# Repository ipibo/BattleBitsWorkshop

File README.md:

# BattleBitsWorkshop
Repo with info about the Battle Bits Workshop

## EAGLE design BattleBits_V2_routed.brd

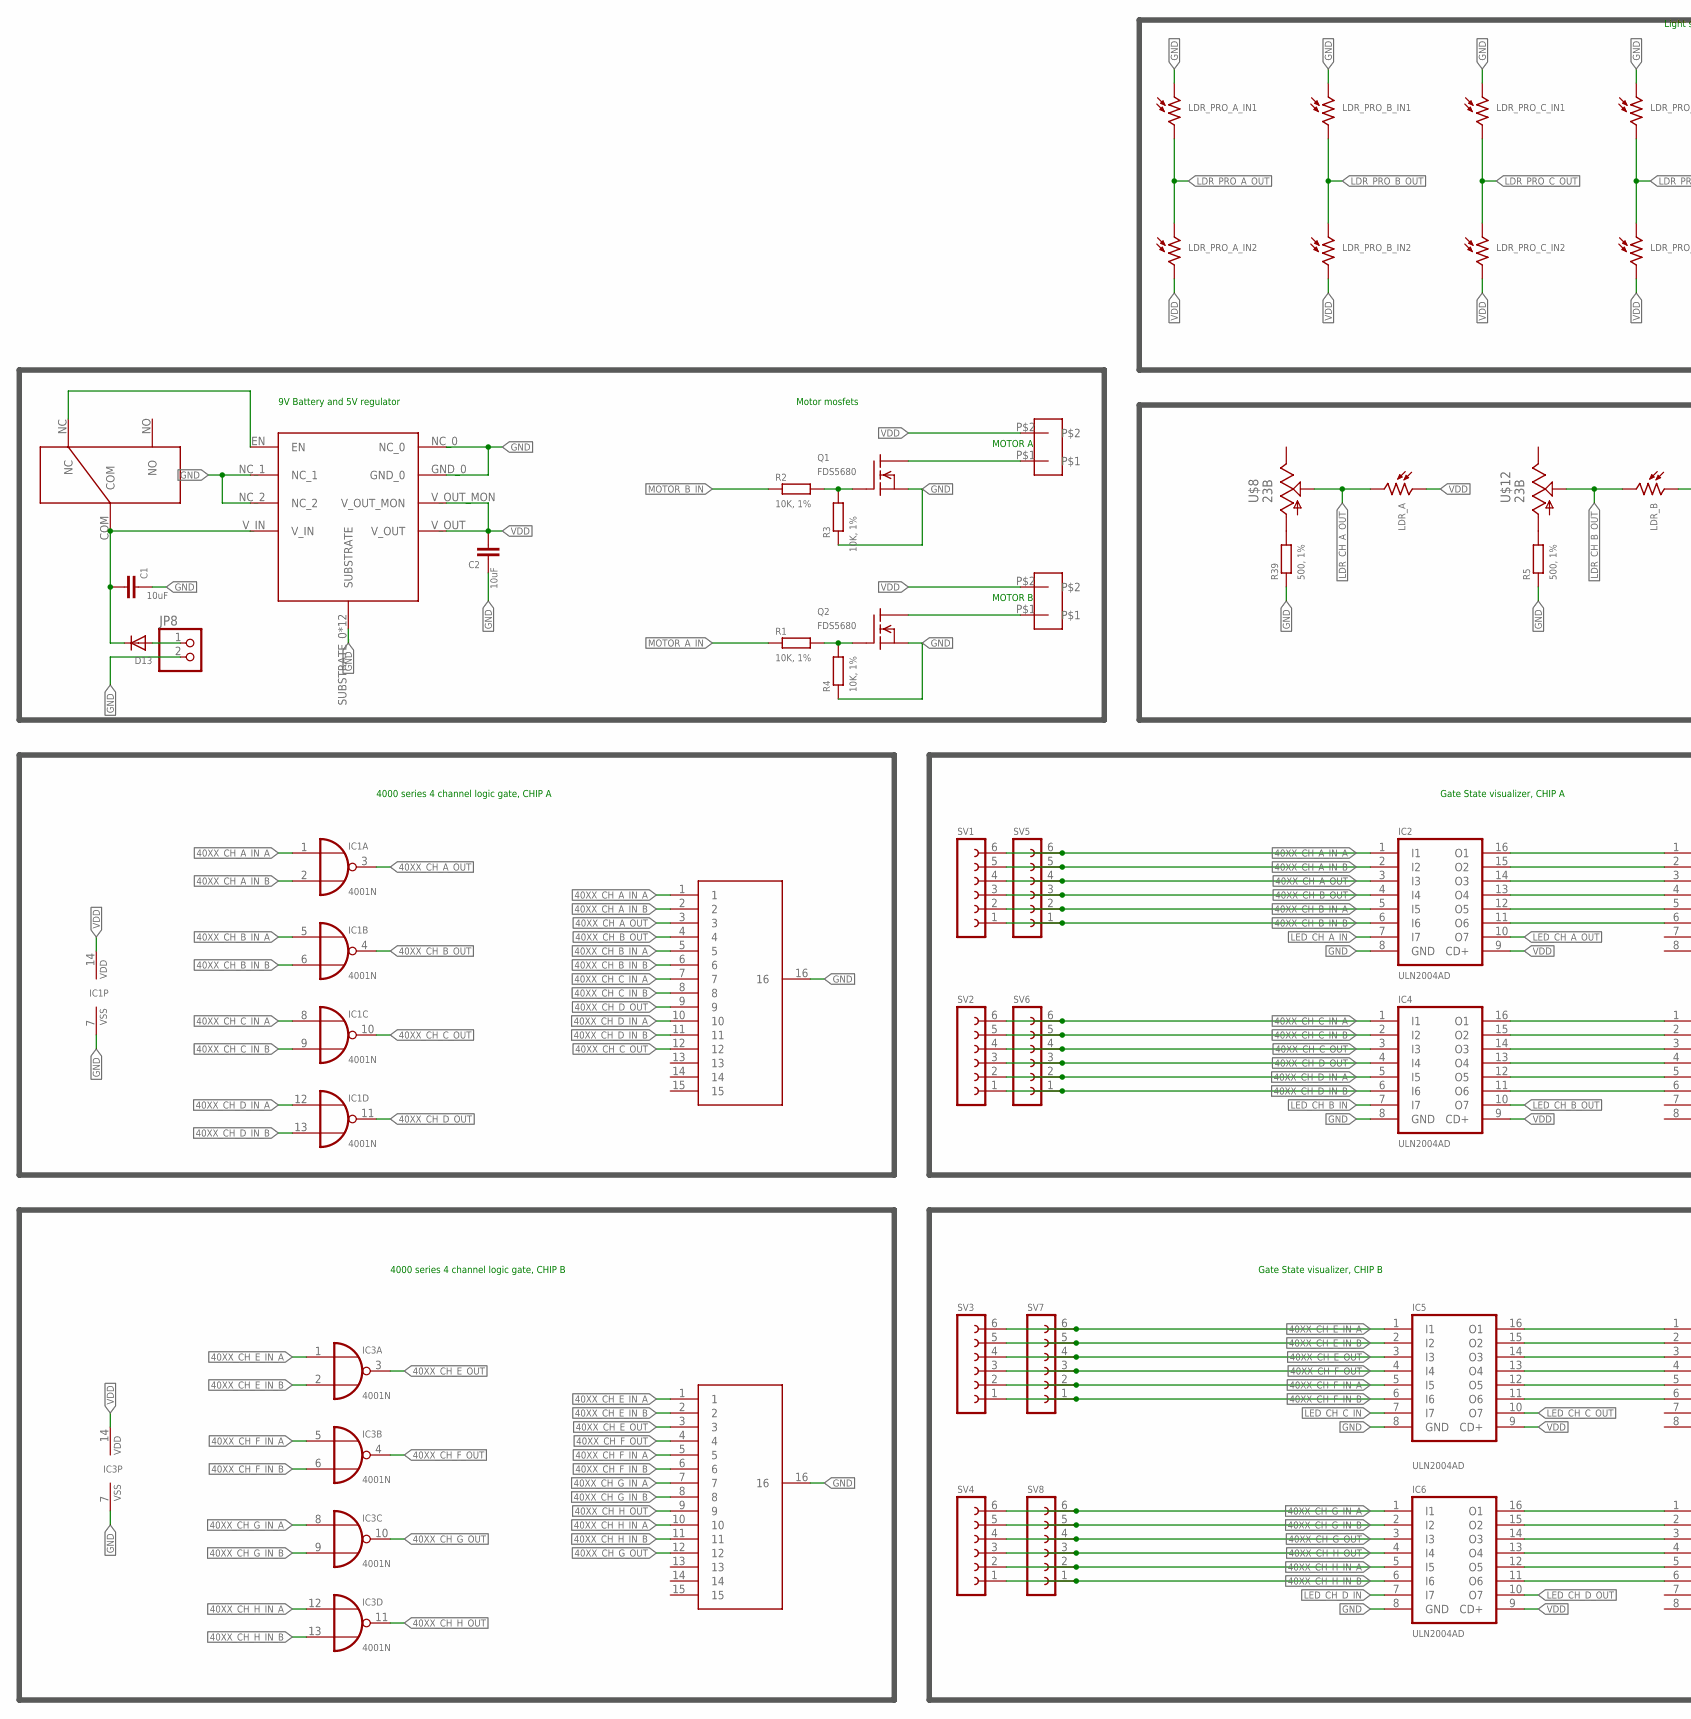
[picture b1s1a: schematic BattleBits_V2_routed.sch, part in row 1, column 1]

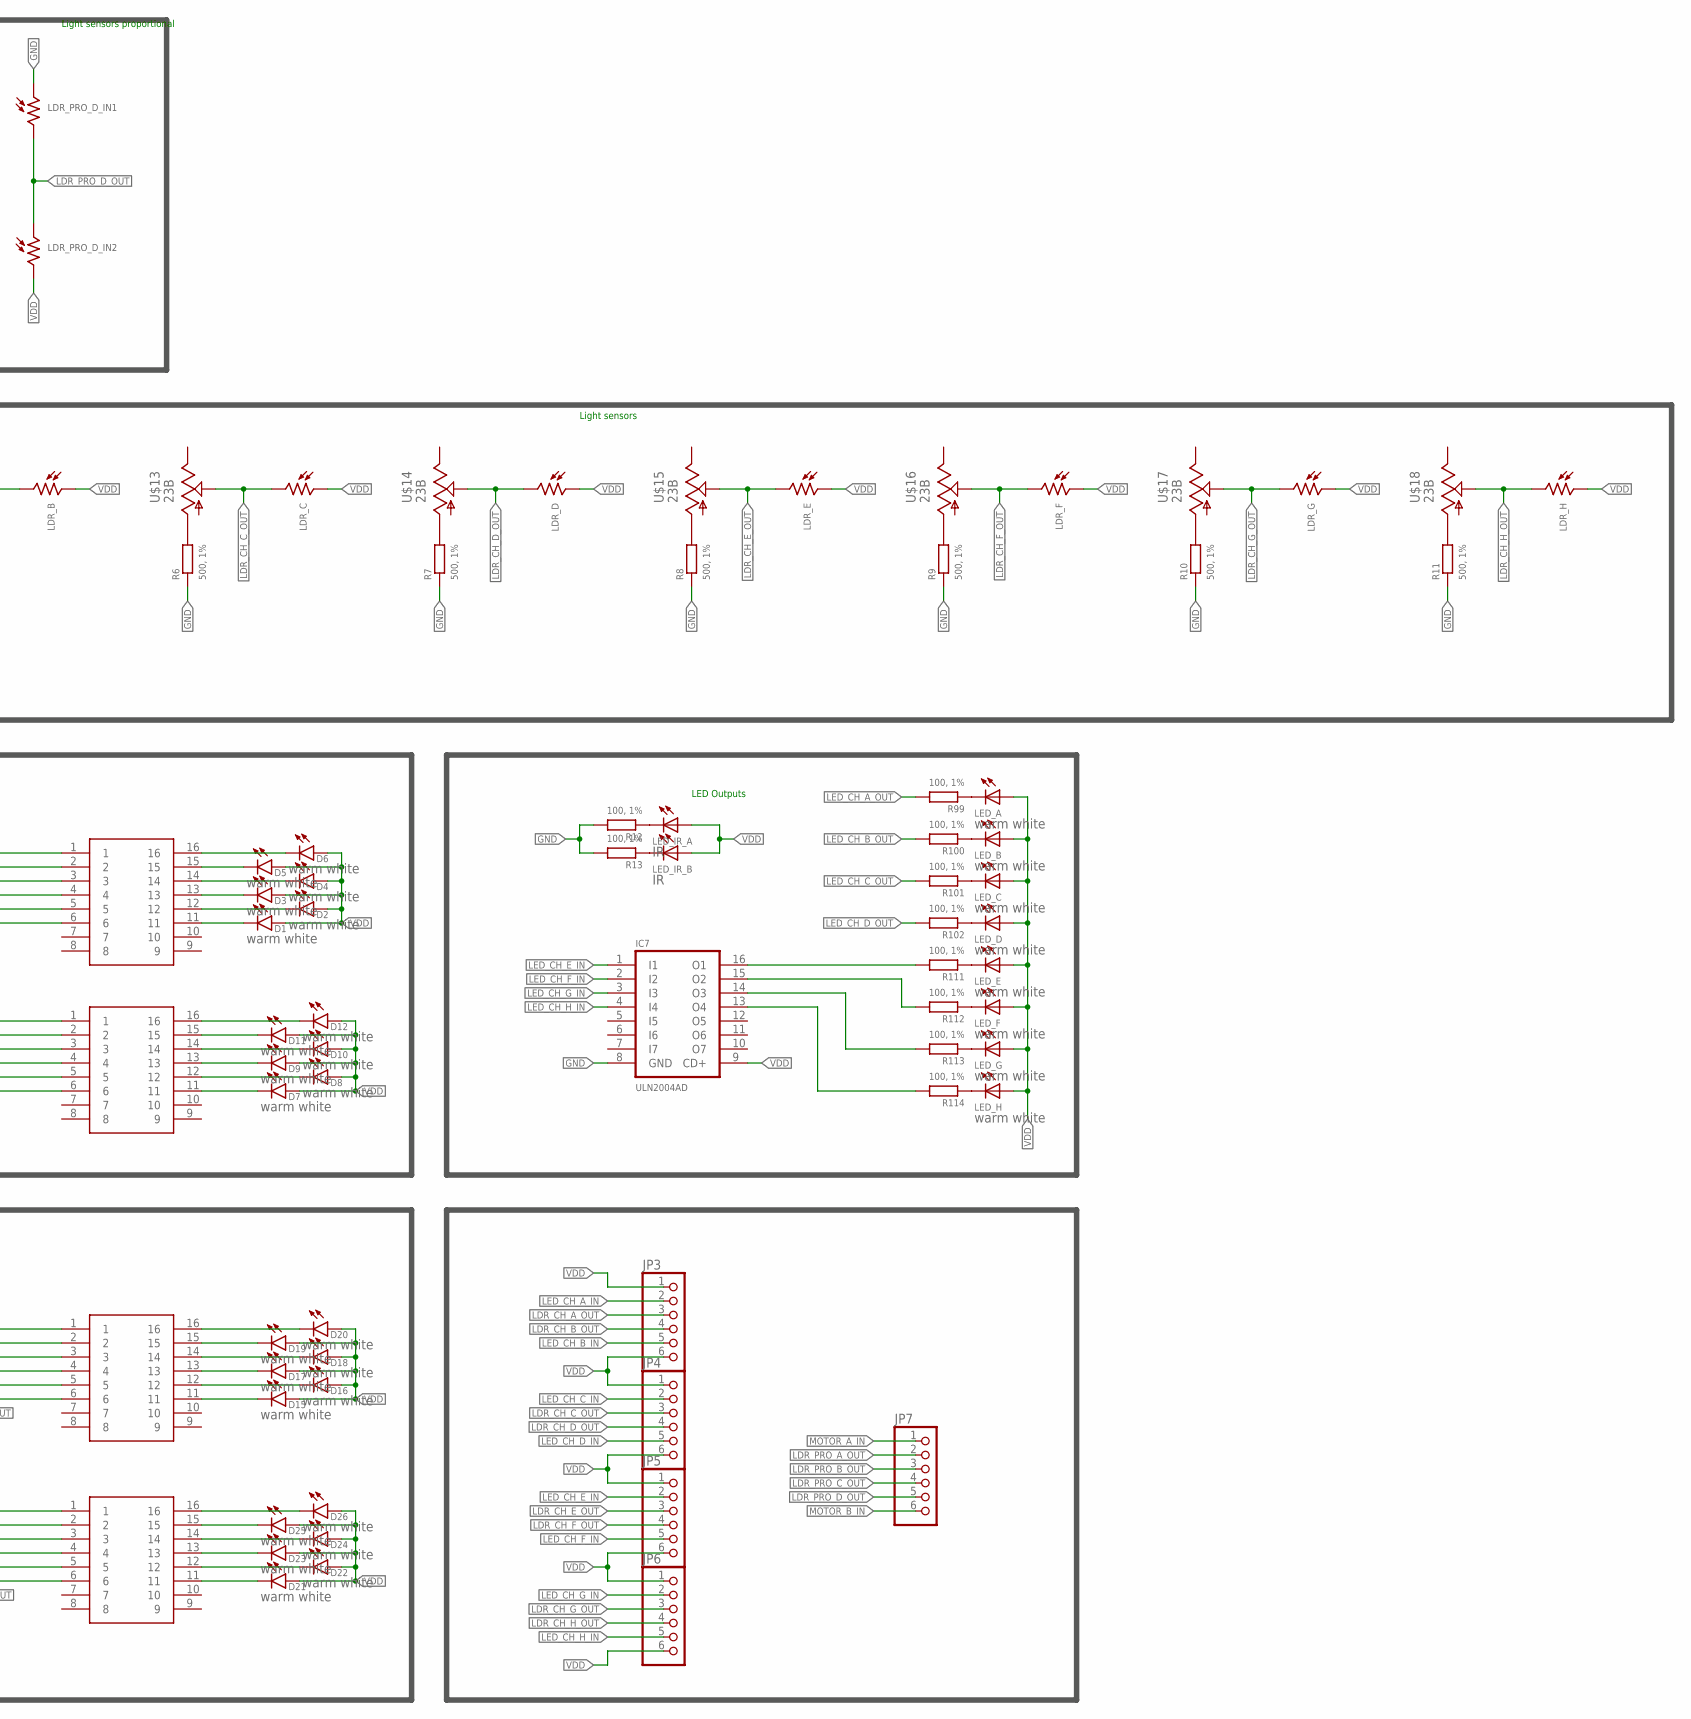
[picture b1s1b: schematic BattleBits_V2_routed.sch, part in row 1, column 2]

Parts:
C1, C2: 10uF; C3216
D1, D2, D3, D4, D5, D6, D7, D8, D9, D10, D11, D12, D15, D16, D17, D18, D19, D20, D21, D22, D23, D24, D25, D26: warm white; LED-1206
D13: DIODESMA; SMADIODE
IC1, IC3: 4001N; DIL14
IC2, IC4, IC5, IC6, IC7: ULN2004AD; SO16
JP3, JP4, JP5, JP6, JP7: PINHD-1X6; 1X06
JP8: PINHD-1X2; 1X02
LDR_A: V1060_21; TO-5_V10
LDR_B: V1060_21; TO-5_V10
LDR_C: V1060_21; TO-5_V10
LDR_D: V1060_21; TO-5_V10
LDR_E: V1060_21; TO-5_V10
LDR_F: V1060_21; TO-5_V10
LDR_G: V1060_21; TO-5_V10
LDR_H: V1060_21; TO-5_V10
LDR_PRO_A_IN1, LDR_PRO_A_IN2: V1060_21; TO-5_V10
LDR_PRO_B_IN1, LDR_PRO_B_IN2: V1060_21; TO-5_V10
LDR_PRO_C_IN1, LDR_PRO_C_IN2: V1060_21; TO-5_V10
LDR_PRO_D_IN1, LDR_PRO_D_IN2: V1060_21; TO-5_V10
LED_A: warm white; LED5MM
LED_B: warm white; LED5MM
LED_C: warm white; LED5MM
LED_D: warm white; LED5MM
LED_E: warm white; LED5MM
LED_F: warm white; LED5MM
LED_G: warm white; LED5MM
LED_H: warm white; LED5MM
LED_IR_A: IR; LED5MM
LED_IR_B: IR; LED5MM
Q1, Q2: FDS5680; SO-8
R1, R2, R3, R4: 10K, 1%; R3216
R5, R6, R7, R8, R9, R10, R11, R39: 500, 1%; R3216
R12, R13, R99, R100, R101, R102, R111, R112, R113, R114: 100, 1%; R3216
SV1, SV2, SV3, SV4, SV5, SV6, SV7, SV8: FE06-1; FE06
U$1, U$2: MOTOR; GEARMOTOR
U$3, U$11: 15_RES_BUS_SOIC16; SO16
U$4: ROHM_LDO; HTSOP-J8
U$5, U$6, U$9, U$10: 8_RES_ISO_SOIC-16; SO16
U$7: SLIDE_SWITCH
U$8, U$12, U$13, U$14, U$15, U$16, U$17, U$18: 23B; 23B-GULL_WING

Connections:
40XX_CH_A_IN_A: IC1.1 (I0), IC2.1 (I1), SV1.6, SV5.6, U$11.1
40XX_CH_A_IN_B: IC1.2 (I1), IC2.2 (I2), SV1.5, SV5.5, U$11.2
40XX_CH_A_OUT: IC1.3 (O), IC2.3 (I3), SV1.4, SV5.4, U$11.3
40XX_CH_B_IN_A: IC1.5 (I0), IC2.5 (I5), SV1.2, SV5.2, U$11.5
40XX_CH_B_IN_B: IC1.6 (I1), IC2.6 (I6), SV1.1, SV5.1, U$11.6
40XX_CH_B_OUT: IC1.4 (O), IC2.4 (I4), SV1.3, SV5.3, U$11.4
40XX_CH_C_IN_A: IC1.8 (I0), IC4.1 (I1), SV2.6, SV6.6, U$11.7
40XX_CH_C_IN_B: IC1.9 (I1), IC4.2 (I2), SV2.5, SV6.5, U$11.8
40XX_CH_C_OUT: IC1.10 (O), IC4.3 (I3), SV2.4, SV6.4, U$11.12
40XX_CH_D_IN_A: IC1.12 (I0), IC4.5 (I5), SV2.2, SV6.2, U$11.10
40XX_CH_D_IN_B: IC1.13 (I1), IC4.6 (I6), SV2.1, SV6.1, U$11.11
40XX_CH_D_OUT: IC1.11 (O), IC4.4 (I4), SV2.3, SV6.3, U$11.9
40XX_CH_E_IN_A: IC3.1 (I0), IC5.1 (I1), SV3.6, SV7.6, U$3.1
40XX_CH_E_IN_B: IC3.2 (I1), IC5.2 (I2), SV3.5, SV7.5, U$3.2
40XX_CH_E_OUT: IC3.3 (O), IC5.3 (I3), SV3.4, SV7.4, U$3.3
40XX_CH_F_IN_A: IC3.5 (I0), IC5.5 (I5), SV3.2, SV7.2, U$3.5
40XX_CH_F_IN_B: IC3.6 (I1), IC5.6 (I6), SV3.1, SV7.1, U$3.6
40XX_CH_F_OUT: IC3.4 (O), IC5.4 (I4), SV3.3, SV7.3, U$3.4
40XX_CH_G_IN_A: IC3.8 (I0), IC6.1 (I1), SV4.6, SV8.6, U$3.7
40XX_CH_G_IN_B: IC3.9 (I1), IC6.2 (I2), SV4.5, SV8.5, U$3.8
40XX_CH_G_OUT: IC3.10 (O), IC6.3 (I3), SV4.4, SV8.4, U$3.12
40XX_CH_H_IN_A: IC3.12 (I0), IC6.5 (I5), SV4.2, SV8.2, U$3.10
40XX_CH_H_IN_B: IC3.13 (I1), IC6.6 (I6), SV4.1, SV8.1, U$3.11
40XX_CH_H_OUT: IC3.11 (O), IC6.4 (I4), SV4.3, SV8.3, U$3.9
GND: C1.1, C2.1, IC1.7 (VSS), IC2.8 (GND), IC3.7 (VSS), IC4.8 (GND), IC5.8 (GND), IC6.8 (GND), IC7.8 (GND), JP8.2, LDR_PRO_A_IN1.1, LDR_PRO_B_IN1.1, LDR_PRO_C_IN1.1, LDR_PRO_D_IN1.1, Q1.1 (S), Q1.2 (S), Q1.3 (S), Q2.1 (S), Q2.2 (S), Q2.3 (S), R3.1, R4.1, R5.1, R6.1, R7.1, R8.1, R9.1, R10.1, R11.1, R12.2, R13.2, R39.1, U$3.16, U$4.GND_0, U$4.NC_0, U$4.NC_1, U$4.NC_2, U$4.SUBSTRATE_0 (SUBSTRATE), U$4.SUBSTRATE_1 (SUBSTRATE), U$4.SUBSTRATE_2 (SUBSTRATE), U$4.SUBSTRATE_3 (SUBSTRATE), U$4.SUBSTRATE_4 (SUBSTRATE), U$4.SUBSTRATE_5 (SUBSTRATE), U$4.SUBSTRATE_6 (SUBSTRATE), U$4.SUBSTRATE_7 (SUBSTRATE), U$4.SUBSTRATE_8 (SUBSTRATE), U$4.SUBSTRATE_9 (SUBSTRATE), U$4.SUBSTRATE_10 (SUBSTRATE), U$4.SUBSTRATE_11 (SUBSTRATE), U$11.16
LDR_CH_A_OUT: JP3.3, LDR_A.2, U$8.2
LDR_CH_B_OUT: JP3.4, LDR_B.2, U$12.2
LDR_CH_C_OUT: JP4.3, LDR_C.2, U$13.2
LDR_CH_D_OUT: JP4.4, LDR_D.2, U$14.2
LDR_CH_E_OUT: JP5.3, LDR_E.2, U$15.2
LDR_CH_F_OUT: JP5.4, LDR_F.2, U$16.2
LDR_CH_G_OUT: JP6.3, LDR_G.2, U$17.2
LDR_CH_H_OUT: JP6.4, LDR_H.2, U$18.2
LDR_PRO_A_OUT: JP7.2, LDR_PRO_A_IN1.2, LDR_PRO_A_IN2.1
LDR_PRO_B_OUT: JP7.3, LDR_PRO_B_IN1.2, LDR_PRO_B_IN2.1
LDR_PRO_C_OUT: JP7.4, LDR_PRO_C_IN1.2, LDR_PRO_C_IN2.1
LDR_PRO_D_OUT: JP7.5, LDR_PRO_D_IN1.2, LDR_PRO_D_IN2.1
LED_CH_A_IN: IC2.7 (I7), JP3.2
LED_CH_A_OUT: IC2.10 (O7), R99.2
LED_CH_B_IN: IC4.7 (I7), JP3.5
LED_CH_B_OUT: IC4.10 (O7), R100.2
LED_CH_C_IN: IC5.7 (I7), JP4.2
LED_CH_C_OUT: IC5.10 (O7), R101.2
LED_CH_D_IN: IC6.7 (I7), JP4.5
LED_CH_D_OUT: IC6.10 (O7), R102.2
LED_CH_E_IN: IC7.1 (I1), JP5.2
LED_CH_F_IN: IC7.2 (I2), JP5.5
LED_CH_G_IN: IC7.3 (I3), JP6.2
LED_CH_H_IN: IC7.4 (I4), JP6.5
MOTOR_A-: Q1.5 (D), Q1.6 (D), Q1.7 (D), Q1.8 (D), U$1.P$1
MOTOR_A_IN: JP7.1, R1.1
MOTOR_B-: Q2.5 (D), Q2.6 (D), Q2.7 (D), Q2.8 (D), U$2.P$1
MOTOR_B_IN: JP7.6, R2.1
unnamed: IC2.16 (O1), U$5.1
unnamed: Q1.4 (G), R2.2, R3.2
unnamed: Q2.4 (G), R1.2, R4.2
unnamed: IC2.15 (O2), U$5.2
unnamed: IC2.14 (O3), U$5.3
unnamed: IC2.13 (O4), U$5.4
unnamed: IC2.12 (O5), U$5.5
unnamed: IC2.11 (O6), U$5.6
unnamed: IC6.16 (O1), U$10.1
unnamed: IC4.16 (O1), U$6.1
unnamed: IC4.15 (O2), U$6.2
unnamed: IC4.14 (O3), U$6.3
unnamed: IC4.13 (O4), U$6.4
unnamed: IC4.12 (O5), U$6.5
unnamed: IC4.11 (O6), U$6.6
unnamed: D6.C, U$5.16
unnamed: IC6.14 (O3), U$10.3
unnamed: D5.C, U$5.15
unnamed: IC5.16 (O1), U$9.1
unnamed: D4.C, U$5.14
unnamed: IC5.15 (O2), U$9.2
unnamed: D3.C, U$5.13
unnamed: IC5.14 (O3), U$9.3
unnamed: D2.C, U$5.12
unnamed: IC5.13 (O4), U$9.4
unnamed: D1.C, U$5.11
unnamed: IC5.12 (O5), U$9.5
unnamed: IC5.11 (O6), U$9.6
unnamed: IC6.15 (O2), U$10.2
unnamed: IC6.13 (O4), U$10.4
unnamed: IC6.12 (O5), U$10.5
unnamed: D12.C, U$6.16
unnamed: D11.C, U$6.15
unnamed: IC6.11 (O6), U$10.6
unnamed: D10.C, U$6.14
unnamed: D9.C, U$6.13
unnamed: D8.C, U$6.12
unnamed: D7.C, U$6.11
unnamed: R39.2, U$8.1
unnamed: R5.2, U$12.1
unnamed: IC7.16 (O1), R111.2
unnamed: IC7.15 (O2), R112.2
unnamed: IC7.14 (O3), R113.2
unnamed: IC7.13 (O4), R114.2
unnamed: R6.2, U$13.1
unnamed: R7.2, U$14.1
unnamed: R8.2, U$15.1
unnamed: R9.2, U$16.1
unnamed: R10.2, U$17.1
unnamed: R11.2, U$18.1
unnamed: D13.A, JP8.1
unnamed: U$4.EN, U$7.NC
unnamed: LED_IR_A.K (C), R12.1
unnamed: LED_IR_B.K (C), R13.1
unnamed: D20.C, U$9.16
unnamed: D19.C, U$9.15
unnamed: D18.C, U$9.14
unnamed: D17.C, U$9.13
unnamed: D16.C, U$9.12
unnamed: D15.C, U$9.11
unnamed: D26.C, U$10.16
unnamed: D25.C, U$10.15
unnamed: D24.C, U$10.14
unnamed: D23.C, U$10.13
unnamed: D22.C, U$10.12
unnamed: D21.C, U$10.11
unnamed: LED_A.K (C), R99.1
unnamed: LED_B.K (C), R100.1
unnamed: LED_C.K (C), R101.1
unnamed: LED_D.K (C), R102.1
unnamed: LED_E.K (C), R111.1
unnamed: LED_F.K (C), R112.1
unnamed: LED_G.K (C), R113.1
unnamed: LED_H.K (C), R114.1
VBAT: C1.2, D13.C, U$4.V_IN, U$7.COM
VDD: C2.2, D1.A, D2.A, D3.A, D4.A, D5.A, D6.A, D7.A, D8.A, D9.A, D10.A, D11.A, D12.A, D15.A, D16.A, D17.A, D18.A, D19.A, D20.A, D21.A, D22.A, D23.A, D24.A, D25.A, D26.A, IC1.14 (VDD), IC2.9 (CD+), IC3.14 (VDD), IC4.9 (CD+), IC5.9 (CD+), IC6.9 (CD+), IC7.9 (CD+), JP3.1, JP3.6, JP4.1, JP4.6, JP5.1, JP5.6, JP6.1, JP6.6, LDR_A.1, LDR_B.1, LDR_C.1, LDR_D.1, LDR_E.1, LDR_F.1, LDR_G.1, LDR_H.1, LDR_PRO_A_IN2.2, LDR_PRO_B_IN2.2, LDR_PRO_C_IN2.2, LDR_PRO_D_IN2.2, LED_A.A, LED_B.A, LED_C.A, LED_D.A, LED_E.A, LED_F.A, LED_G.A, LED_H.A, LED_IR_A.A, LED_IR_B.A, U$1.P$2, U$2.P$2, U$4.V_OUT, U$4.V_OUT_MON

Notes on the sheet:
4000 series 4 channel logic gate, CHIP A
9V Battery and 5V regulator
Motor mosfets
MOTOR A
MOTOR B
Gate State visualizer, CHIP A
Light sensors
4000 series 4 channel logic gate, CHIP B
Gate State visualizer, CHIP B
Light sensors proportional
LED Outputs

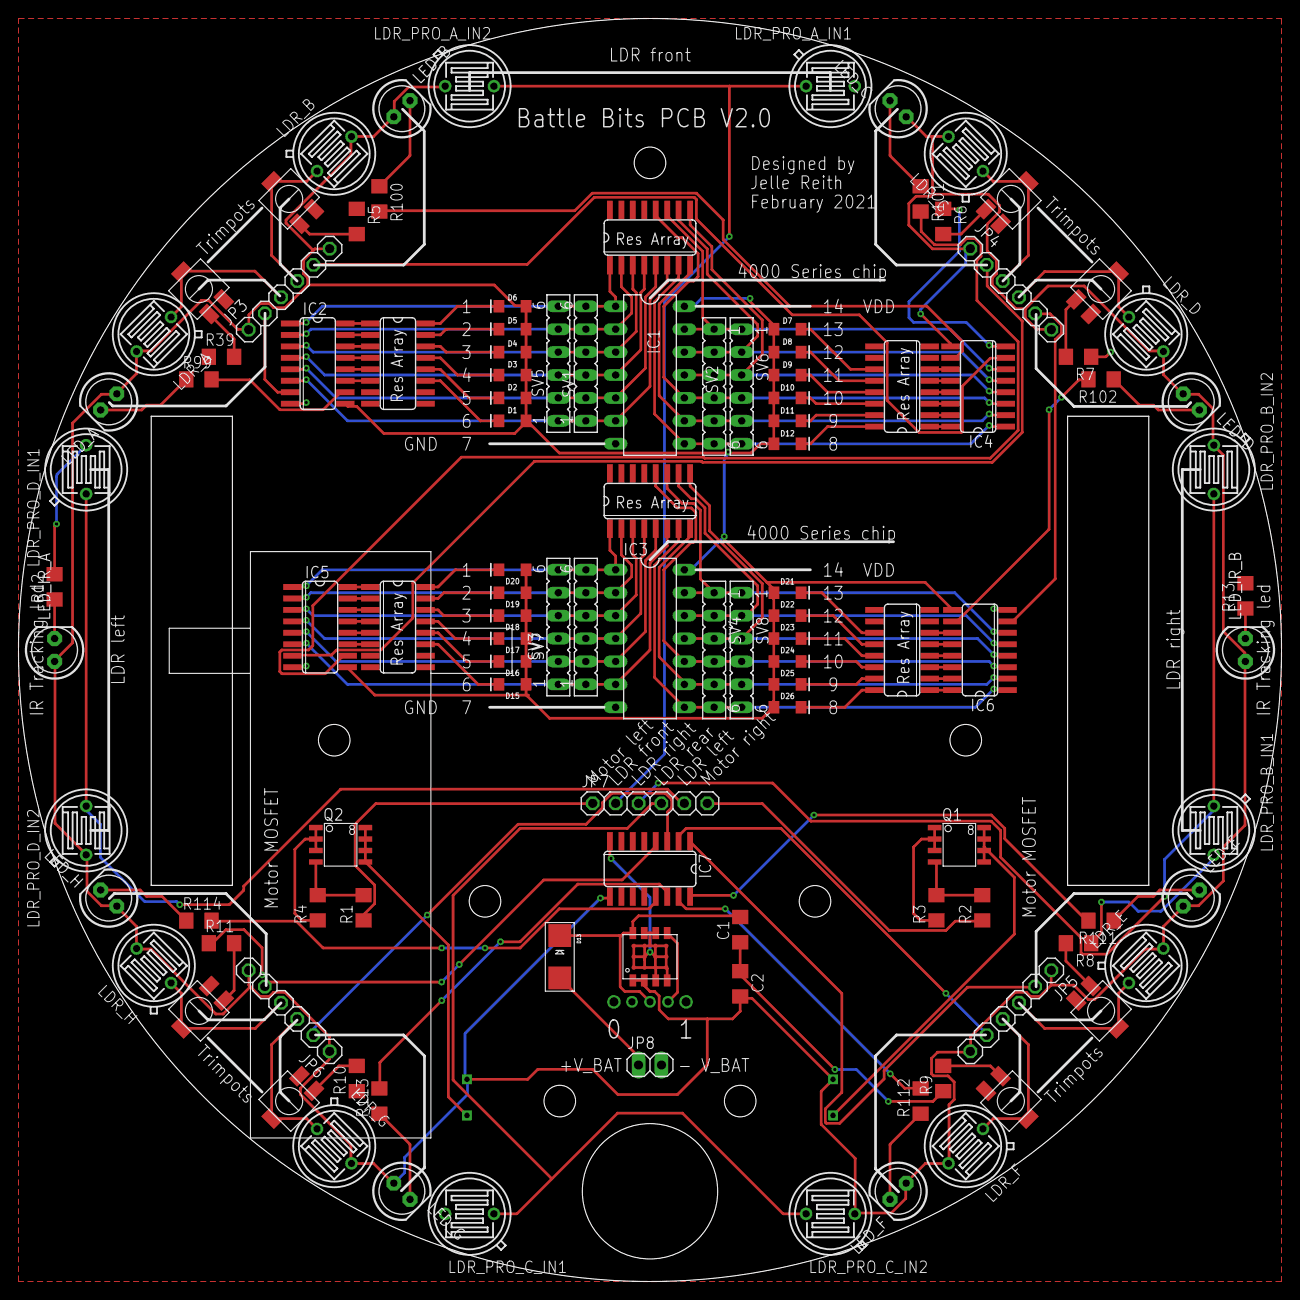
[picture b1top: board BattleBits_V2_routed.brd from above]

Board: 2 copper layers, 140.0 x 140.0 mm, 116 parts (1 on the bottom side), 129 nets.

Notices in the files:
parts and their libraries:
SparkFun-LED: Licensing: Creative Commons ShareAlike 4.0 International - https://creativecommons.org/licenses/by-sa/4.0
